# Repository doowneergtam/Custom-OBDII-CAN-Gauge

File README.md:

# NB1 Miata Gauge

Firmware and hardware notes for a MegaSquirt-fed digital gauge for the
1999-2000 Mazda Miata. Two products, one firmware core:

- `firmware/` — pod gauge on the Waveshare ESP32-S3-Touch-AMOLED-1.75 (first)
- cluster replacement on ESP32-P4 (later, same `components/`)

Docs: [brief](docs/brief.md) · [pod pin map](docs/pod-pinout.md) ·
[MegaSquirt CAN](docs/ms2-can.md) · [decisions](docs/decisions.md)

## Build (Windows, PowerShell)

```powershell
. $HOME\esp\esp-idf\export.ps1
idf.py -C firmware set-target esp32s3
idf.py -C firmware build
idf.py -C firmware -p COM5 flash monitor
```

## Flashing without the toolchain

`firmware/flash/` holds the latest built image and a one-line script for
esptool, so any PC with Python can flash the gauge. See
`firmware/flash/README.md`.

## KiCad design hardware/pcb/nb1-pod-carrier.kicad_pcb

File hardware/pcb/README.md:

# Pod carrier PCB, rev C (two analog inputs, no encoder)

Circular Ø46 mm two-layer board behind the Waveshare ESP32-S3-Touch-AMOLED-1.75.
It plugs into the Waveshare's 8-pin socket with a long-pin header and carries
the input protection, a Traco TSR 1-2450 5 V buck, a socket for a WCMCU-230
(SN65HVD230) CAN module, the headlight opto-sense, two conditioned analog
sensor inputs, and two HY2.0 connectors (car harness, sensors). Parts and
both connectors sit on the rear face, cables leave rearward. Bottom copper
faces the Waveshare; a sparse top copper layer (17 short tracks) carries the
crossings, joined by 9 rivet vias.

Rules: 2.25 mm pads, 1.0 mm holes (1.2 mm TVS, 0.9 mm HY2.0), 0.6 mm signal /
1.0 mm power and ground / 0.8 mm 3V3 tracks, 0.8 mm from the edge. Clearance
is 0.42 mm on this board (0603 chip parts in the sensor cluster); the checker
accepts 0.35 mm, so use a 0.2 mm isolation cut. This is finer than the rev B
rules, as agreed, because the sensor network would not fit at 0.5 mm.

## Files

| File | What |
|---|---|
| `gen_pcb.py` | Parts and placement (jumper positions overridable with `NB1_SJ1`, `NB1_SJ2`). |
| `gen_tracks.py` | Routing driver: net order, widths, hand-seeded stubs and vias, cached seed. |
| `router.py` | Two-layer grid router with rivet vias; top tracks only end on axial leads, chip pads or vias. |
| `drc.py`, `export_islands.py` | Crossing/clearance/edge/connectivity checks (geometric and shapely islands). |
| `sweep.py` | Tries jumper placements and reports which route cleanly. |
| `ascii_map.py`, `svg_preview.py` | Text map (`NB1_MAP_LAYER=1` for top) and the labelled preview. |
| `mill/nb1_carrier_copper_bottom_view.svg` | **Cut this first**: bottom copper, mirrored, with outline and drill layers by size. |
| `mill/nb1_carrier_copper_top_view.svg` | **Then flip and cut this**: top copper, parts-side view, not mirrored, same frame. |
| `mill/nb1_carrier_drill_only.svg`, `_copper_only.svg`, `_assembly_top_view.svg` | Drills alone, copper alone, placement with refs and pin names. |
| `assembly_sheet.py`, `mill/nb1_carrier_assembly_sheet.svg` | Blown-up assembly drawing with leader-line labels, pin numbers, via and top-side markings, and the BOM with part numbers. |
| `nb1-pod-carrier.kicad_pcb` | KiCad 8 file of the same board. |

```bash
python hardware/pcb/gen_pcb.py && python hardware/pcb/drc.py
```
Delete `best_seed.txt` after moving parts so the router searches again.

## Milling and assembly order

1. Mill the bottom (mirrored file), drill all holes, flip on two of the M2
   holes as your registration, mill the top (not mirrored).
2. Fit the 9 vias (1.0 mm holes): copper rivets swaged both sides, or trimmed resistor leads soldered
   both sides. The assembly sheet rings each one in its own colour (via key under the board). Positions, parts-side
   view, mm from the centre:

   | Via | Net | x | y |
   |---|---|---|---|
   | VL | LIGHTS | −2.0 | 12.0 |
   | VP5 | 5V | 11.1 | −11.0 |
   | VA1 | AIN1 | −5.5 | −12.0 |
   | V4 | NODE1 | −14.15 | −4.9 |
   | V5 | NODE2 | −11.65 | 1.1 |
   | V6 | AIN2 | −6.15 | −0.9 |
   | V7 | 5V | −12.15 | −9.65 |
   | V8 | GND | −7.65 | 1.85 |
   | V9 | GND | 2.1 | 8.6 |

3. Solder the 0603 parts and the two solder jumpers on the TOP side (they sit
   left of the CAN module, beside the sensor connector).
4. Fit the through-hole parts from the top and solder on the bottom. Three
   axial leads also carry a top-side track and must be soldered on the top as
   well: **D1 pin 1, D2 pin 1, R2 pin 2** (the top end). Everything else is
   bottom only.
5. J1: long-pin header, body on top, pins through into the Waveshare socket.

## Sensor inputs

Per input: sensor → 1 kΩ → GPIO, 1.5 kΩ GPIO → GND, so 0 to 5 V reads as 0 to
3 V. Solder jumper closed adds a 1 kΩ pull-up from 5 V at the sensor node for
resistive (temperature) senders; open for 0 to 5 V senders. SJ1 is input 1
(GPIO17, J3 pin 3), SJ2 is input 2 (GPIO18, J3 pin 4). J3: 5V, GND, SENS1,
SENS2. Firmware filtering replaces the input capacitor.

Build note (2026-10-24): on this gauge **SJ2 is bridged**, so input 2 (AIN2, J3 pin 4, GPIO18) is a
resistive temperature sender; SJ1 stays open. Set the Input 2 card on the phone page to resistive
with the sender's ohms-to-temperature points so the firmware matches the jumper.

## Connectors and header

| J1 pin | Net | J2 (car) | J3 (sensors) |
|---|---|---|---|
| 1 IO18 | AIN2 | 1 GND | 1 5V out |
| 2 IO17 | AIN1 | 2 LIGHTS | 2 GND |
| 3 IO16 | unused | 3 CAN L | 3 SENS1 |
| 4 IO44 | CAN_TX | 4 CAN H | 4 SENS2 |
| 5 IO43 | CAN_RX via R3 | 5 12 V ign | |
| 6 3V3 | 3V3 | | |
| 7 GND | GND | | |
| 8 VBUS | 5V | | |

## Next revision wishlist

- Replace the solder bridges SJ1/SJ2 with something you can change without an iron: a 2-pin
  2.54 mm header per input with a jumper cap, or a 2-position DIP switch (one position per input).
  Same net pair as the bridge (sensor node to the 1 kΩ pull-up), so only the footprint changes.
  Asked for at the rev C bench build, 2026-10-24.

## Verify before milling

1. WCMCU-230 pin order (`CAN_MODULE_PINS` in `gen_pcb.py`): module reads
   `3V3 GND CTX CRX CANH CANL`, mounted rotated so it lands `CANL CANH CRX CTX GND 3V3`.
2. Traco pin 1 (+Vin) is the left pin of U1; D1 and D2 bands toward pin 1 (left).
3. C1 and C2 positive is pin 2 (right pad).
4. Mounting holes match the Waveshare at (±13.75, −14.70) and (0, +20.50),
   3.4 mm rings. The top ring sits 0.8 mm from the edge, which is the rule limit.

## Bill of materials (rev C)

| Ref | Part |
|---|---|
| J1 | 1x8 long-pin header 2.54 mm |
| J2 | HY2.0-5P vertical |
| J3 | HY2.0-4P vertical |
| J5 | 1x3 pads, wires to Waveshare EX0 / SDA / SCL |
| U2 + socket | WCMCU-230 CAN module, 1x6 female header |
| U1 | Traco TSR 1-2450 |
| F1 | Polyfuse 1.1 A 30 V radial |
| D1 | 1N5822 |
| D2 | P6KE33A or SMBJ26A on leads |
| C1 | 47 µF 50 V, 2.54 pitch |
| C2 | 100 µF 10 V, 2.54 pitch |
| R2 | 2.2 kΩ 1/4 W |
| R3 | 1 kΩ 1/4 W |
| U3 | PC817 |
| R11, R21, RP1, RP2 | 1 kΩ 0603 |
| R12, R22 | 1.5 kΩ 0603 |
| SJ1, SJ2 | solder-bridge pads |
| V* | 9 × 1.0 mm copper rivets |

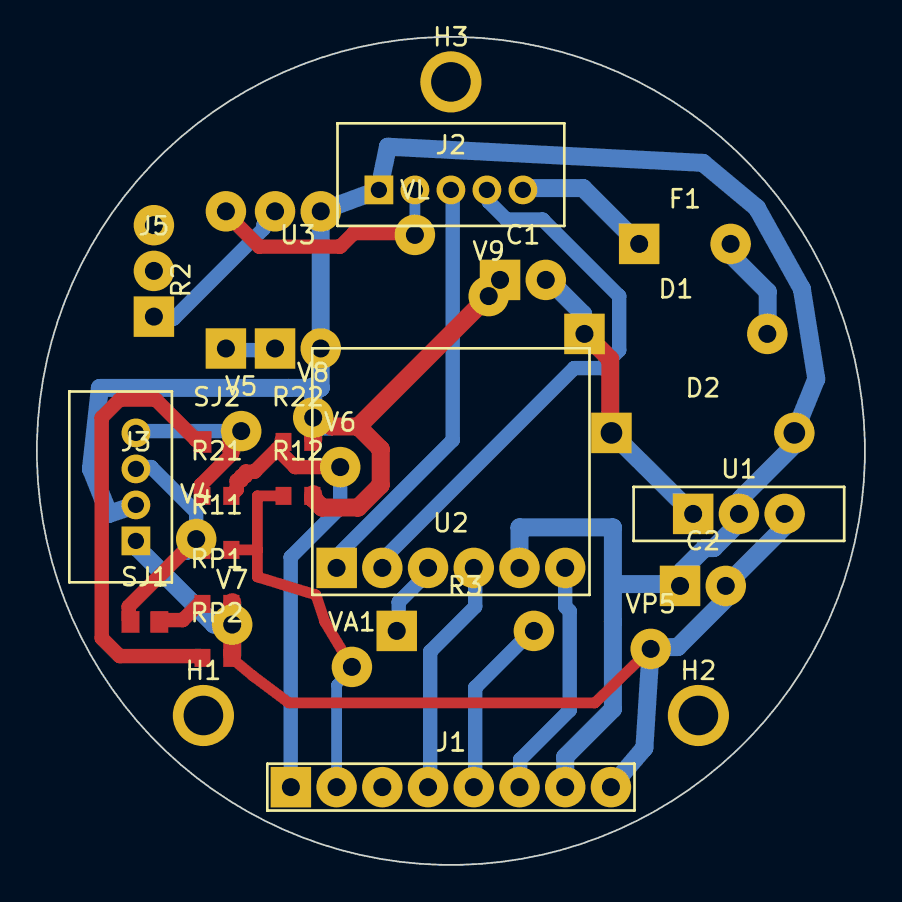
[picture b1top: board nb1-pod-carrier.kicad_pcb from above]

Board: 2 copper layers, 46.0 x 46.0 mm, 34 parts (0 on the bottom side), 20 nets.

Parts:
C1: 47uF 50V; CP_Radial_P2.54
C2: 100uF 10V; CP_Radial_P2.54
D1: 1N5822; D_DO-201_P10.16
D2: P6KE33A; D_DO-15_P10.16
F1: Polyfuse 1.1A 30V; Fuse_Radial_P5.08
H1, H2, H3: M2 mount; MountingHole_2.2mm_Ring3.4
J1: to Waveshare 1x8; PinHeader_1x08_P2.54mm_LongPins
J2: HY2.0-5P car; HY2.0_1x05_Vertical
J3: HY2.0-4P sensors; HY2.0_1x04_Vertical
J5: EX0 SDA SCL wires; PinHeader_1x03_P2.54mm
R2: 2k2; R_Axial_P7.62
R3: 1k; R_Axial_P7.62
R11, R21: 1k; R_0603
R12, R22: 1k5; R_0603
RP1, RP2: 1k; R_0603
SJ1, SJ2: bridge=resistive; SolderJumper_2
U1: TSR 1-2450; SIP-3_P2.54mm
U2: WCMCU-230 CAN module; WCMCU-230_1x06
U3: PC817; DIP-4_W7.62mm
V4, V5, V6, V7, V8, V9: via; Via_Rivet
VA1: via; Via_Rivet
VL: via; Via_Rivet
VP5: via; Via_Rivet

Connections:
3V3: J1.6, U2.6
5V: C2.2, J1.8, J3.1, RP1.2, RP2.2, U1.3, V7.1, VP5.1
12V_F: D1.2, F1.2
12V_IN: F1.1, J2.5
12V_P: C1.2, D1.1, D2.1, U1.1
AIN1: J1.2, R11.2, R12.1, VA1.1
AIN2: J1.1, R21.2, R22.1, V6.1
CANH: J2.4, U2.2
CANL: J2.3, U2.1
CAN_RX: J1.5, R3.2
CAN_RXM: R3.1, U2.3
CAN_TX: J1.4, U2.4
EX0: J5.1, U3.4
GND: C1.1, C2.1, D2.2, J1.7, J2.1, J3.2, R12.2, R22.2, U1.2, U2.5, U3.2, U3.3, V8.1, V9.1
LED_K: R2.1, U3.1
LIGHTS: J2.2, R2.2, VL.1
NODE1: J3.3, R11.1, SJ1.1, V4.1
NODE2: J3.4, R21.1, SJ2.2, V5.1
PU1: RP1.1, SJ1.2
PU2: RP2.1, SJ2.1

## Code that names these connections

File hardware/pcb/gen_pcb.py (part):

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
# WCMCU-230: 15.45 x 13.7 mm, one 1x6 header along one edge. Pin order as read
# on the module silkscreen, pin 1 first. EDIT THIS to match your module.
CAN_MODULE_PINS = ["CANL", "CANH", "CAN_RXM", "CAN_TX", "GND", "3V3"]   # module rotated 180 deg so CRX/CTX sit above J1 pins 4/5

b = Board("NB1 pod carrier rev B")

# ------------------------------------------------------------ parts
# J1 pin use (rev C): IO18 AIN2, IO17 AIN1, IO16 unused, RXD(44) CAN_TX, TXD(43) CAN_RX via R3, 3V3, GND, VBUS
b.footprint("J1", "to Waveshare 1x8", "PinHeader_1x08_P2.54mm_LongPins", (0, HEADER_Y),
            pads=header_row(8, names=["AIN2", "AIN1", "", "CAN_TX", "CAN_RX", "3V3", "GND", "5V"]),
            silk=[(-10.2, -1.3, 10.2, -1.3), (-10.2, 1.3, 10.2, 1.3), (-10.2, -1.3, -10.2, 1.3), (10.2, -1.3, 10.2, 1.3)],
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b.footprint("J3", "HY2.0-4P sensors", "HY2.0_1x04_Vertical", (-17.5, -2.0),
            pads=header_row(4, pitch=2.0, pad=1.6, drill=0.9, names=["5V", "GND", "NODE1", "NODE2"], vertical=True),
            silk=[(-3.7, -5.3, 2.0, -5.3), (-3.7, 5.3, 2.0, 5.3), (-3.7, -5.3, -3.7, 5.3), (2.0, -5.3, 2.0, 5.3)],
            desc="Sensors: 5 V out for 0-5 V senders, GND, AIN1, AIN2. Pin 1 (5V) at the bottom")

# Per channel: node -> R1 1k -> GPIO, R2 1.5k GPIO -> GND (always in: scales 0-5 V to 0-3 V, limits current).
# JP closed adds RP 1k from 5 V to the node for resistive (thermistor) senders; open for 0-5 V senders.
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_SJ2 = tuple(float(v) for v in os.environ.get("NB1_SJ2", "-13.0,0.5").split(","))
b.footprint("SJ2", "bridge=resistive", "SolderJumper_2", _SJ2, pads=smd2(nets=("PU2", "NODE2"), **PSJ), desc="Solder bridge (top side): closed = resistive sender on input 2, open = 0-5 V sender")
b.footprint("RP1", "1k", "R_0603", (-13.0, -8.5), pads=smd2(nets=("PU1", "5V"), **P06), desc="Pull-up 1k from 5 V, in circuit when SJ1 is bridged (top side)")
b.footprint("R11", "1k", "R_0603", (-13.0, -5.5), pads=smd2(nets=("NODE1", "AIN1"), **P06), desc="Series 1k, sensor node 1 to GPIO17 (top side)")
b.footprint("R21", "1k", "R_0603", (-13.0, -2.5), pads=smd2(nets=("NODE2", "AIN2"), **P06), desc="Series 1k, sensor node 2 to GPIO18 (top side)")
b.footprint("SJ1", "bridge=resistive", "SolderJumper_2", _SJ1, pads=smd2(nets=("NODE1", "PU1"), **PSJ), desc="Solder bridge (top side): closed = resistive sender on input 1, open = 0-5 V sender")
b.footprint("R12", "1k5", "R_0603", (-8.5, -2.5), pads=smd2(nets=("AIN1", "GND"), **P06), desc="1.5k GPIO17 to GND: with R11 scales 5 V to 3 V (top side)")
b.footprint("R22", "1k5", "R_0603", (-8.5, 0.5), pads=smd2(nets=("AIN2", "GND"), **P06), desc="1.5k GPIO18 to GND: with R21 scales 5 V to 3 V (top side)")

b.footprint("J5", "EX0 SDA SCL wires", "PinHeader_1x03_P2.54mm", (-16.5, 10.0),
            pads=header_row(3, names=["EX0", "SDA", "SCL"], vertical=True),
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# R3: 1k in the CAN RX line. GPIO43 carries the ROM boot log for ~300 ms at reset while the
# transceiver also drives it; 1k limits that contention. Its body also carries CAN_RX over CAN_TX.
b.footprint("R3", "1k", "R_Axial_P7.62", (0.8, -10.0), pads=axial(7.62, nets=("CAN_RXM", "CAN_RX")),
            top_ok=True, desc="1k between module CRX (pin 1, left) and header RXD/GPIO43 (pin 2, right); CAN_TX passes underneath")

# input protection chain, right side, top to bottom
b.footprint("F1", "Polyfuse 1.1A 30V", "Fuse_Radial_P5.08", (13.0, 11.5), pads=radial(5.08, nets=("12V_IN", "12V_F")), desc="Resettable fuse, Bourns MF-R110")
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b.footprint("C2", "100uF 10V", "CP_Radial_P2.54", (14.0, -7.5), pads=radial(2.54, nets=("GND", "5V")), desc="5 V output bulk, + is pin 2 (right), - pin 1 (left)")
# headlight sense, left side: 12 V -> R2 -> opto LED; transistor pulls EX0 low
b.footprint("R2", "2k2", "R_Axial_P7.62", (-12.5, 9.5), rot=90, pads=axial(7.62, nets=("LED_K", "LIGHTS")), top_ok=True, desc="Opto LED limit, ~5 mA at 12 V")
b.footprint("U3", "PC817", "DIP-4_W7.62mm", (-8.5, 9.5), pads=dip4(["LED_K", "GND", "GND", "EX0"]),
            desc="1 anode (from R2), 2 cathode (GND), 3 emitter (GND), 4 collector (EX0). Lights on = EX0 low")

# ------------------------------------------------------------ mounting holes (match the Waveshare)
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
